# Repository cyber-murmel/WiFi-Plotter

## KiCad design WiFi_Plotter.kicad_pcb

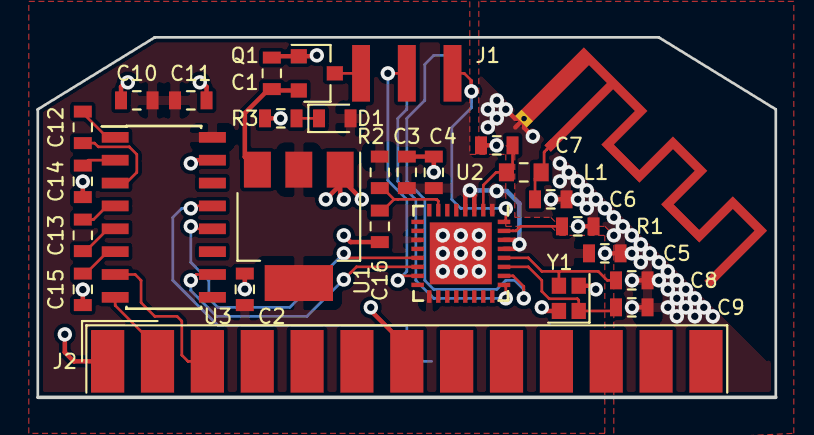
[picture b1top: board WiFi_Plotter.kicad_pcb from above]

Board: 2 copper layers, 41.0 x 20.0 mm, 29 parts (1 on the bottom side), 26 nets.

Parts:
AE1: Antenna_Shield; Texas_SWRA117D_2.4GHz_Right
C1, C2, C3: 10u; C_0603_1608Metric
C4, C10, C12, C13, C14, C15, C16: 100n; C_0603_1608Metric
C5: 1u; C_0603_1608Metric
C6: 2.4p; C_0603_1608Metric
C7: 3.0p; C_0603_1608Metric
C8, C9: 6.8p; C_0603_1608Metric
C11: 1n; C_0603_1608Metric
D1: LED; LED_0603_1608Metric
J1: Conn_02x03_Odd_Even; PinHeader_2x03_P2.54mm_EdgeMount_SMD
J2: DB25_Male; DSUB-25_Male_EdgeMount_P2.77mm
L1: 2.2n; L_0603_1608Metric_Pad0.84x1.00mm_HandSolder
Q1: AO3401; SOT-23
R1, R2, R3: 12k; R_0603_1608Metric
U1: AZ1117-3.3; SOT-223-3_TabPin2
U2: ESP8266EX; QFN-32-1EP_5x5mm_P0.5mm_EP3.45x3.45mm
U3: MAX3232; SOIC-16_3.9x9.9mm_P1.27mm
Y1: 40MHz; Crystal_SMD_2016-4Pin_2.0x1.6mm

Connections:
+3V3: C2.1, C3.1, C4.1, C5.1, C10.1, C11.1, D1.2, R2.2, U1.2, U2.1, U2.3, U2.4, U2.11, U2.17, U2.29, U2.30, U3.16
+VDC: C1.1, Q1.2, U1.3
DTR: J2.20, U3.13
GND: AE1.2, C1.2, C2.2, C3.2, C4.2, C5.2, C6.2, C7.2, C8.1, C9.1, C10.2, C11.2, C14.1, C15.1, C16.1, J1.5, J2.1, J2.7, Q1.1, R1.2, R3.1, U1.1, U2.33, U3.15, Y1.2, Y1.4
MODE: J1.4, U2.15
unnamed: AE1.1, C6.1, L1.1
unnamed: C7.1, L1.2, U2.2
unnamed: C8.2, U2.28, Y1.3
unnamed: C9.2, U2.27, Y1.1
unnamed: C12.1, U3.1
unnamed: C12.2, U3.3
unnamed: C13.1, U3.4
unnamed: C13.2, U3.5
unnamed: C14.2, U3.2
unnamed: C15.2, U3.6
unnamed: C16.2, R2.1, U2.7
unnamed: D1.1, R3.2
unnamed: J1.6, Q1.3
unnamed: R1.1, U2.31
READY: U2.13, U3.12
RESET: J1.2, U2.32
RX: J2.3, U3.7
TX: J2.2, U3.8
UART0_RXD: J1.3, U2.25
UART0_TXD: J1.1, U2.26
UART1_TXD: U2.14, U3.10

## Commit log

2018-07-23 moved files from other repo
